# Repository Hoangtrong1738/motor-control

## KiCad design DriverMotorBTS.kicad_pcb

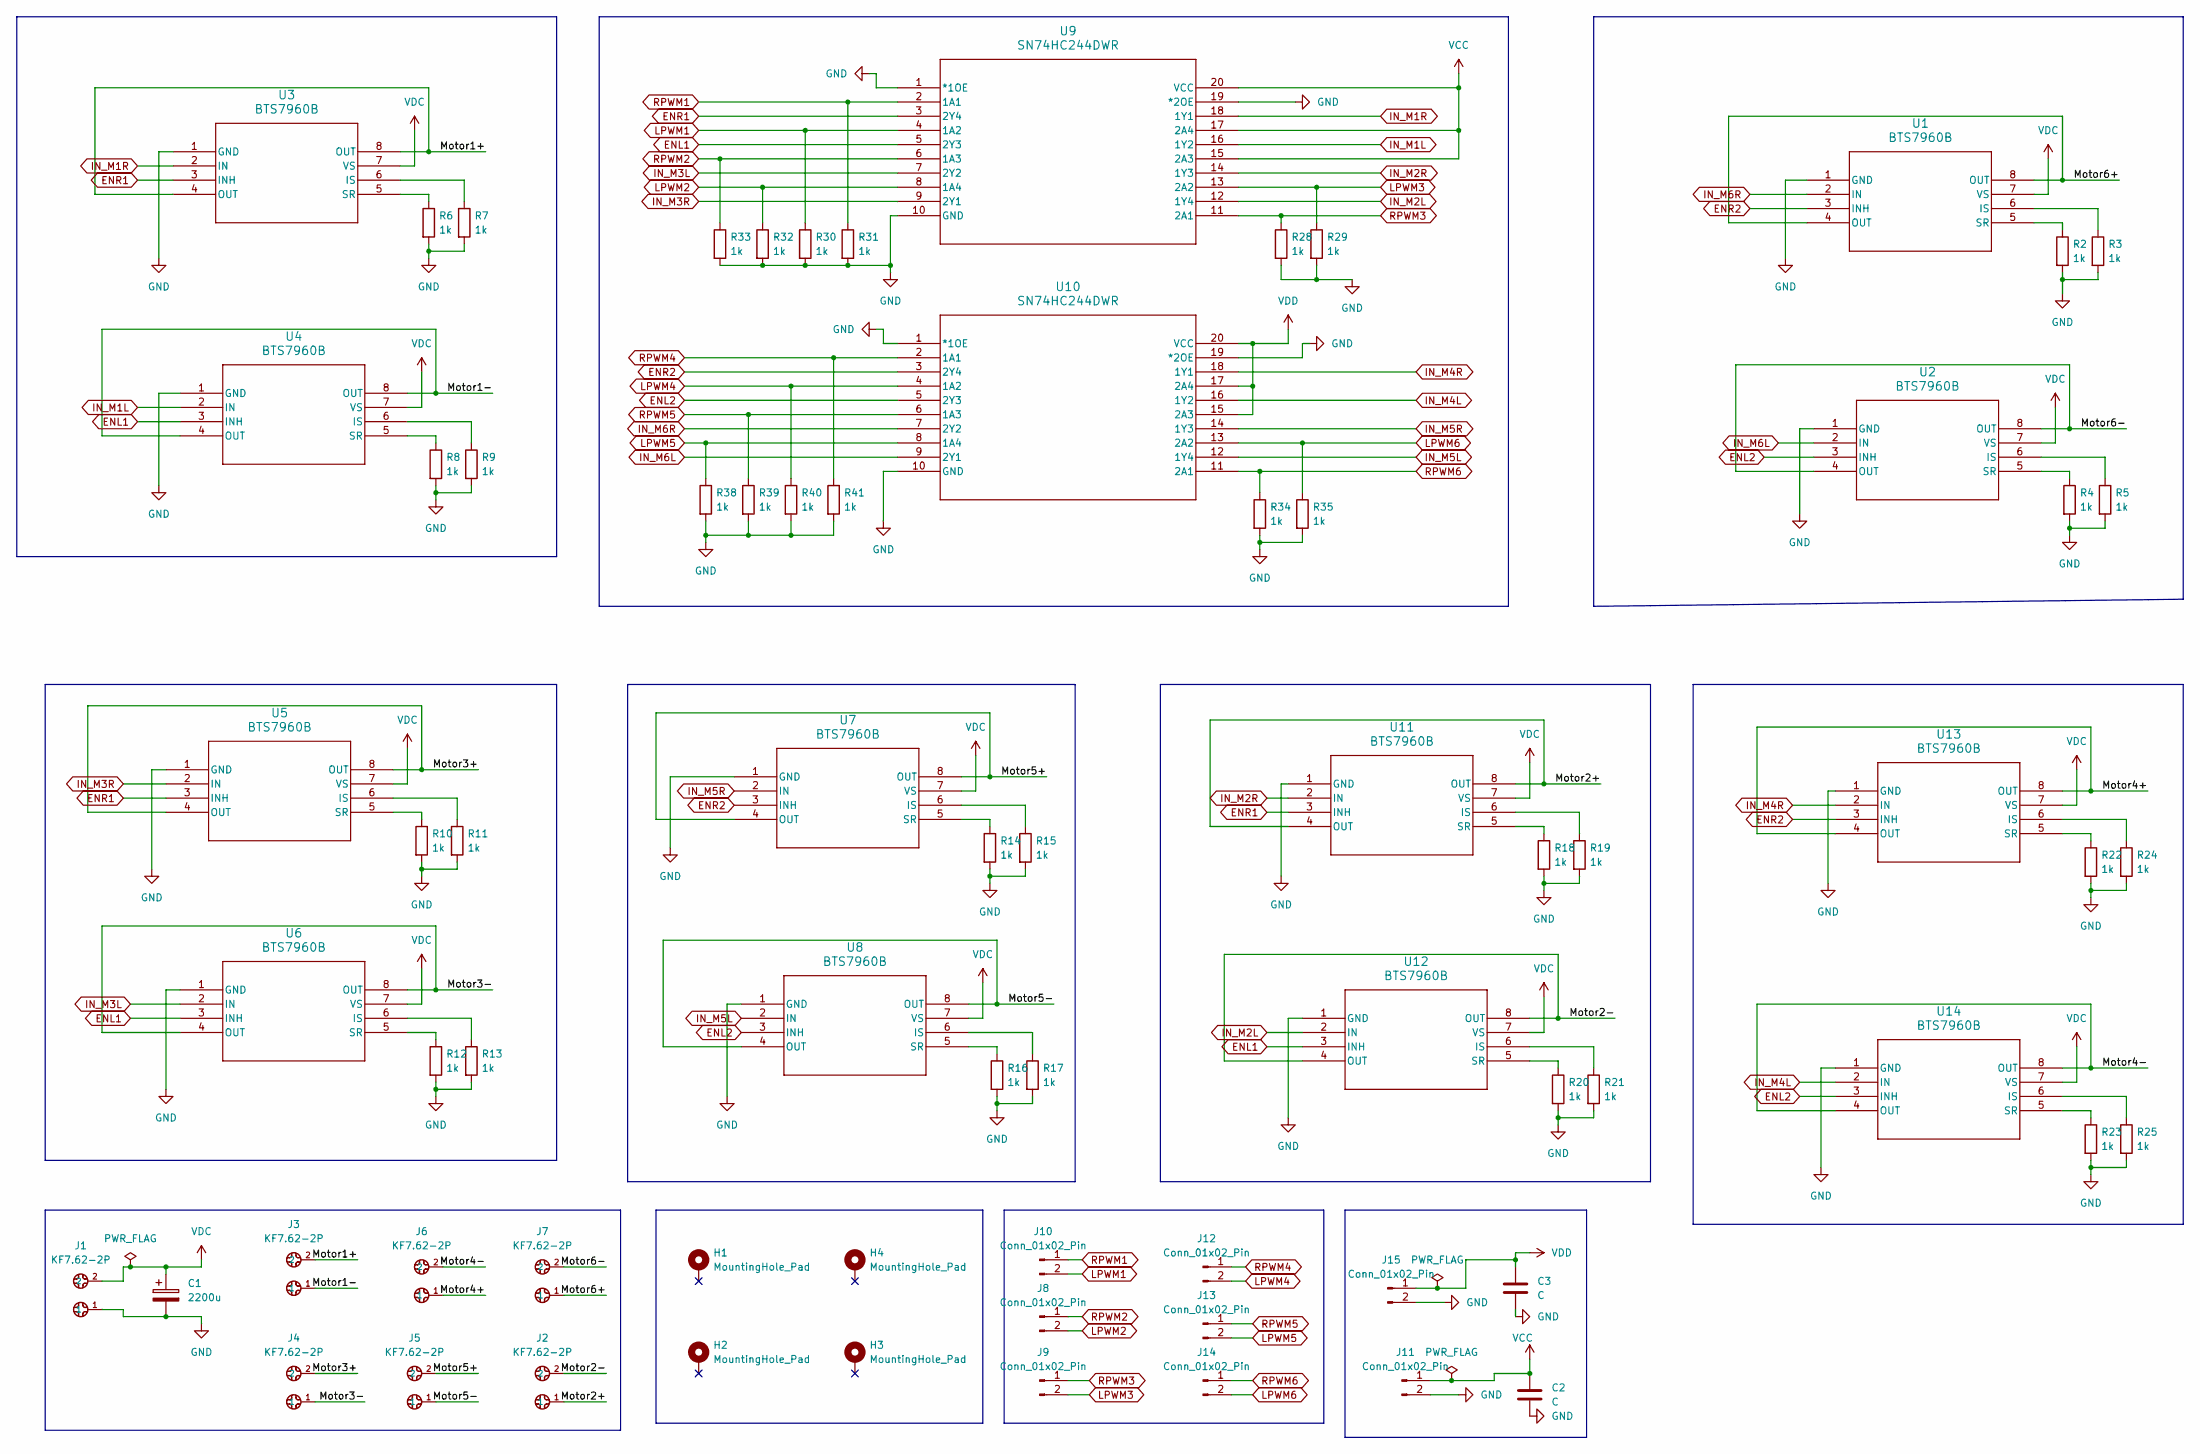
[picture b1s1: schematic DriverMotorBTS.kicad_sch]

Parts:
C1: 2200u; CP_Radial_D16.0mm_P7.50mm
C2, C3: C; C_1206_3216Metric
H1, H2, H3, H4: MountingHole_Pad; MountingHole_2.2mm_M2_Pad_Via
J1, J2, J3, J4, J5, J6, J7: KF7.62-2P; 2P
J8, J9, J10, J11, J12, J13, J14, J15: Conn_01x02_Pin; JST_XH_B2B-XH-A_1x02_P2.50mm_Vertical
R2, R3, R4, R5, R6, R7, R8, R9, R10, R11, R12, R13, R14, R15, R16, R17, R18, R19, R20, R21, R22, R23, R24, R25, R28, R29, R30, R31, R32, R33, R34, R35, R38, R39, R40, R41: 1k; R_0805_2012Metric
U1, U2, U3, U4, U5, U6, U7, U8, U11, U12, U13, U14: BTS7960B; BTS7960B_INF
U9, U10: SN74HC244DWR; DW20

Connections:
/Motor1+: J3.2, U3.4 (OUT), U3.8 (OUT)
/Motor1-: J3.1, U4.4 (OUT), U4.8 (OUT)
/Motor2+: J2.1, U11.4 (OUT), U11.8 (OUT)
/Motor2-: J2.2, U12.4 (OUT), U12.8 (OUT)
/Motor3+: J4.2, U5.4 (OUT), U5.8 (OUT)
/Motor3-: J4.1, U6.4 (OUT), U6.8 (OUT)
/Motor4+: J6.1, U13.4 (OUT), U13.8 (OUT)
/Motor4-: J6.2, U14.4 (OUT), U14.8 (OUT)
/Motor5+: J5.2, U7.4 (OUT), U7.8 (OUT)
/Motor5-: J5.1, U8.4 (OUT), U8.8 (OUT)
/Motor6+: J7.1, U1.4 (OUT), U1.8 (OUT)
/Motor6-: J7.2, U2.4 (OUT), U2.8 (OUT)
ENL1: U4.3 (INH), U6.3 (INH), U9.5 (2Y3), U12.3 (INH)
ENL2: U2.3 (INH), U8.3 (INH), U10.5 (2Y3), U14.3 (INH)
ENR1: U3.3 (INH), U5.3 (INH), U9.3 (2Y4), U11.3 (INH)
ENR2: U1.3 (INH), U7.3 (INH), U10.3 (2Y4), U13.3 (INH)
GND: C1.2, C2.2, C3.2, J1.1, J11.2, J15.2, R2.2, R3.2, R4.2, R5.2, R6.2, R7.2, R8.2, R9.2, R10.2, R11.2, R12.2, R13.2, R14.2, R15.2, R16.2, R17.2, R18.2, R19.2, R20.2, R21.2, R22.2, R23.2, R24.2, R25.2, R28.2, R29.2, R30.2, R31.2, R32.2, R33.2, R34.2, R35.2, R38.2, R39.2, R40.2, R41.2, U1.1 (GND), U2.1 (GND), U3.1 (GND), U4.1 (GND), U5.1 (GND), U6.1 (GND), U7.1 (GND), U8.1 (GND), U9.1 (*1OE), U9.10 (GND), U9.19 (*2OE), U10.1 (*1OE), U10.10 (GND), U10.19 (*2OE), U11.1 (GND), U12.1 (GND), U13.1 (GND), U14.1 (GND)
IN_M1L: U4.2 (IN), U9.16 (1Y2)
IN_M1R: U3.2 (IN), U9.18 (1Y1)
IN_M2L: U9.12 (1Y4), U12.2 (IN)
IN_M2R: U9.14 (1Y3), U11.2 (IN)
IN_M3L: U6.2 (IN), U9.7 (2Y2)
IN_M3R: U5.2 (IN), U9.9 (2Y1)
IN_M4L: U10.16 (1Y2), U14.2 (IN)
IN_M4R: U10.18 (1Y1), U13.2 (IN)
IN_M5L: U8.2 (IN), U10.12 (1Y4)
IN_M5R: U7.2 (IN), U10.14 (1Y3)
IN_M6L: U2.2 (IN), U10.9 (2Y1)
IN_M6R: U1.2 (IN), U10.7 (2Y2)
LPWM1: J10.2, R30.1, U9.4 (1A2)
LPWM2: J8.2, R32.1, U9.8 (1A4)
LPWM3: J9.2, R29.1, U9.13 (2A2)
LPWM4: J12.2, R40.1, U10.4 (1A2)
LPWM5: J13.2, R38.1, U10.8 (1A4)
LPWM6: J14.2, R35.1, U10.13 (2A2)
unnamed: R3.1, U1.6 (IS)
unnamed: R2.1, U1.5 (SR)
unnamed: R5.1, U2.6 (IS)
unnamed: R4.1, U2.5 (SR)
unnamed: R7.1, U3.6 (IS)
unnamed: R6.1, U3.5 (SR)
unnamed: R9.1, U4.6 (IS)
unnamed: R8.1, U4.5 (SR)
unnamed: R11.1, U5.6 (IS)
unnamed: R10.1, U5.5 (SR)
unnamed: R13.1, U6.6 (IS)
unnamed: R12.1, U6.5 (SR)
unnamed: R15.1, U7.6 (IS)
unnamed: R14.1, U7.5 (SR)
unnamed: R17.1, U8.6 (IS)
unnamed: R16.1, U8.5 (SR)
unnamed: R19.1, U11.6 (IS)
unnamed: R18.1, U11.5 (SR)
unnamed: R21.1, U12.6 (IS)
unnamed: R20.1, U12.5 (SR)
unnamed: R24.1, U13.6 (IS)
unnamed: R22.1, U13.5 (SR)
unnamed: R25.1, U14.6 (IS)
unnamed: R23.1, U14.5 (SR)
RPWM1: J10.1, R31.1, U9.2 (1A1)
RPWM2: J8.1, R33.1, U9.6 (1A3)
RPWM3: J9.1, R28.1, U9.11 (2A1)
RPWM4: J12.1, R41.1, U10.2 (1A1)
RPWM5: J13.1, R39.1, U10.6 (1A3)
RPWM6: J14.1, R34.1, U10.11 (2A1)
VCC: C2.1, J11.1, U9.15 (2A3), U9.17 (2A4), U9.20 (VCC)
VDC: C1.1, J1.2, U1.7 (VS), U2.7 (VS), U3.7 (VS), U4.7 (VS), U5.7 (VS), U6.7 (VS), U7.7 (VS), U8.7 (VS), U11.7 (VS), U12.7 (VS), U13.7 (VS), U14.7 (VS)
VDD: C3.1, J15.1, U10.15 (2A3), U10.17 (2A4), U10.20 (VCC)

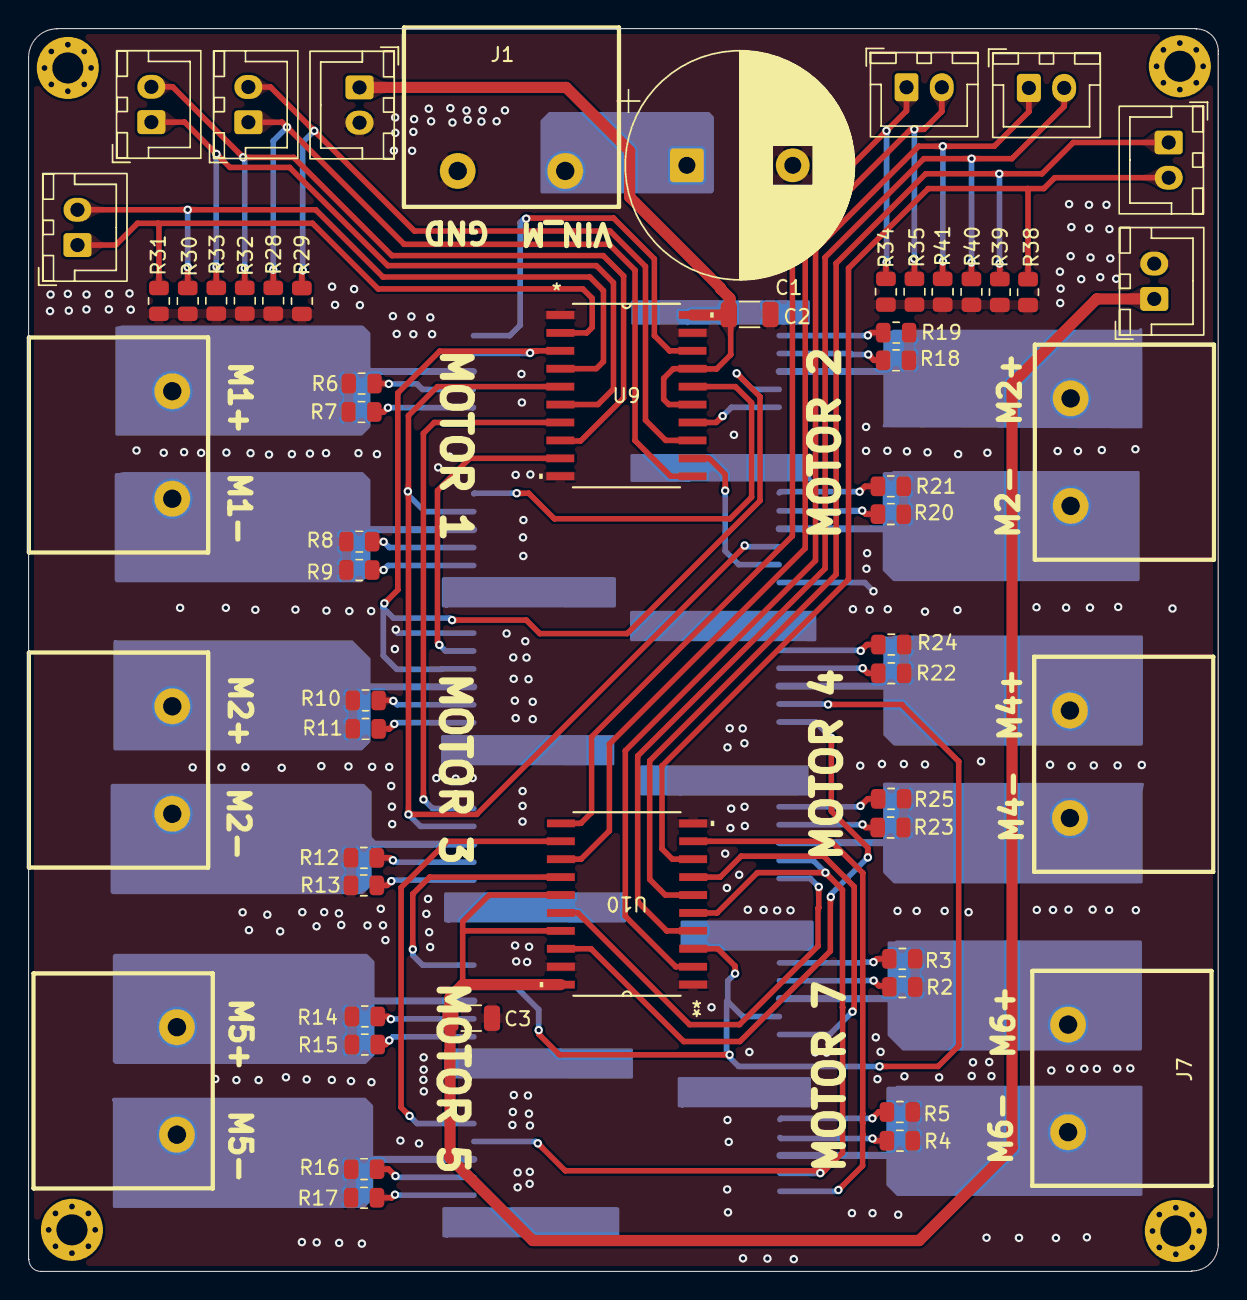
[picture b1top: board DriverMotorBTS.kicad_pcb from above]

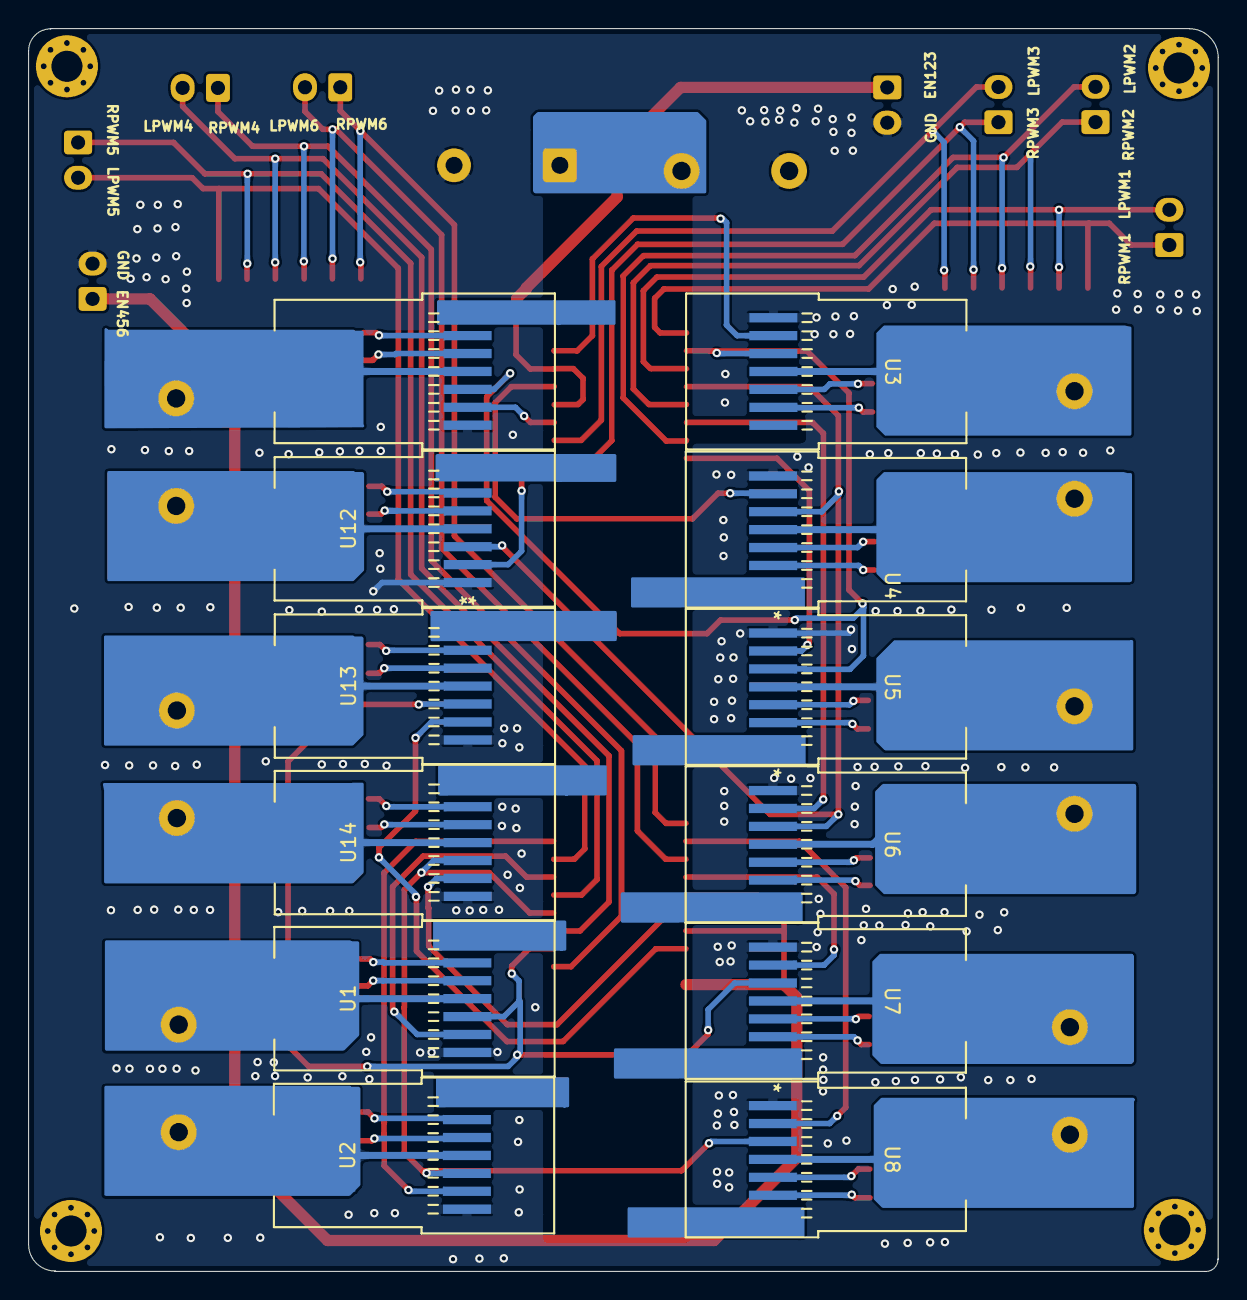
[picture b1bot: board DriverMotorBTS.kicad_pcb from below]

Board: 2 copper layers, 84.3 x 88.1 mm, 72 parts (12 on the bottom side), 68 nets.
